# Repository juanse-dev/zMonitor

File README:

zMonitor

Director:
- Fredy E. Segura Ph.D      (fsegura@uniandes.edu.co)

Autores:
- Juan Sebastian Cifuentes  (j-cifuen@uniandes.edu.co)
- Viviana Salcedo           (vp.salcedo93@uniandes.edu.co)

zMonitor es un dispositivo para la adquisición de señales de EEG y su visualización en Android desarrollado en el curso de Sistemas Embebidos de la Universidad de los Andes.

Se puede ver un video del funcionamiento de zMonitor en http://www.youtube.com/watch?v=pW1bedwvCxc

El proyecto se encuentra organizado por carpetas de la siguiente manera:
- Android: Archivos de la aplicación en Android.
- Microcontrolador: Programa en C para la adquisición de los datos y el envío por bluetooth.
- PCB-Eagle: Circuitos y PCBs en Eagle.
- README: Este archivo.

Características:
- Frecuencia de muestreo: 500Hz
- Resolución del ADC: 10bits
- Ganancia: Variable, de 1 a 100000*
- Banda pasante: 1 - 40Hz por medio de 2 filtros butterworth de 2 y 3 orden.
- Bluetooth baudrate: 57600bps
- Alimentación: Batería Lipo (3.7V)

* Amplificador por arreglar

ToDo:
- Arreglar Amplificador
- Guardar datos en archivo
- Enviar a base de datos
- Visualizador para la base de datos
- Mejorar trigger

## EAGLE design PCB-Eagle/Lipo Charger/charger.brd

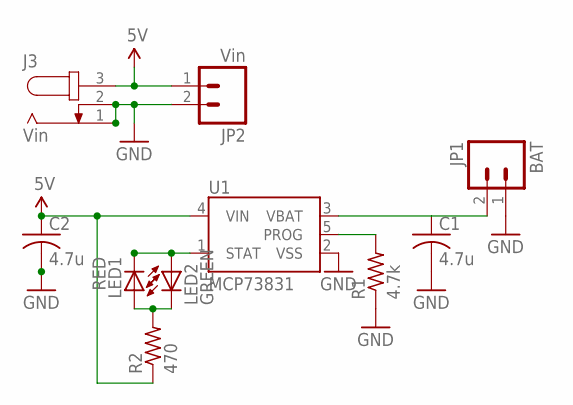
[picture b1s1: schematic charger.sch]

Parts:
C1, C2: 4.7u; C0805
J3: Vin; SPC4077
JP1: BAT; JST-2-PTH
JP2: Vin; 1X02_LOCK_LONGPADS
LED1: RED; SML0805
LED2: GREEN; SML0805
R1: 4.7k; M1206
R2: 470; M1206
U1: MCP73831; SOT23-5

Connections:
5V: C2.1, J3.3, JP2.1, R2.1, U1.4 (VIN)
GND: C1.2, C2.2, J3.1, J3.2, JP1.1, JP2.2, R1.1, U1.2 (VSS)
unnamed: LED1.A, LED2.C, R2.2
unnamed: LED1.C, LED2.A, U1.1 (STAT)
unnamed: R1.2, U1.5 (PROG)
unnamed: C1.1, JP1.2, U1.3 (VBAT)

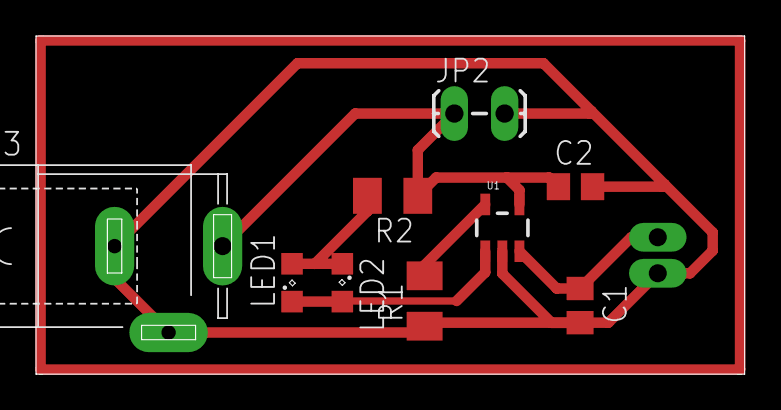
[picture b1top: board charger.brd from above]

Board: 2 copper layers, 39.4 x 18.8 mm, 10 parts (1 on the bottom side), 6 nets.

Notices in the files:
parts and their libraries:
SparkFun: Licensing: CC v3.0 Share-Alike You are welcome to use this library for commercial purposes.
